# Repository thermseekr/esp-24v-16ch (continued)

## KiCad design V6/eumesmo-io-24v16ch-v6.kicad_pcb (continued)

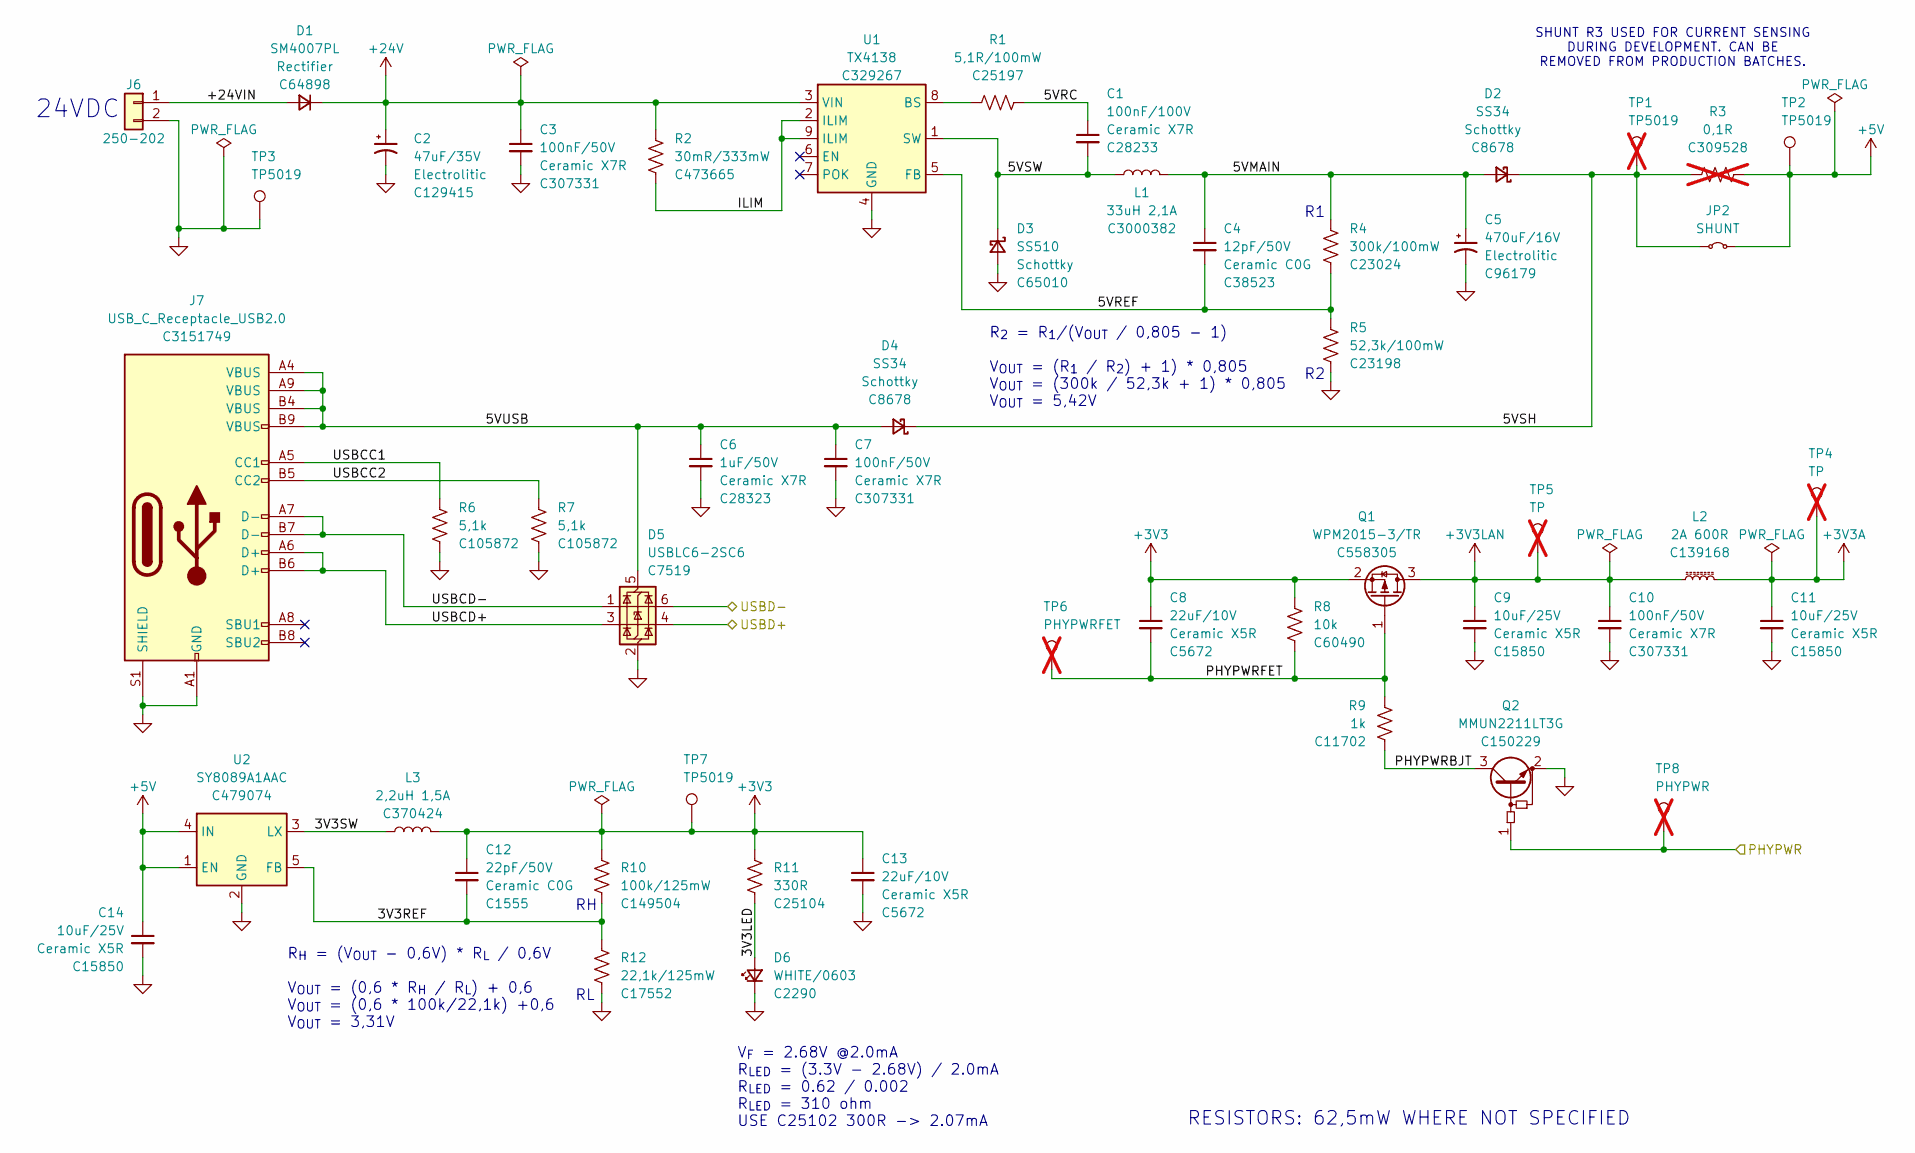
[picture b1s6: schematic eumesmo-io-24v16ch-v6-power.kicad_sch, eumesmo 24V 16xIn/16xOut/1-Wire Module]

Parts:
C1: 100nF/100V; C_0805_2012Metric; Mfr PN CL21B104KCFNNNE; LCSC Part # C28233
C2: 47uF/35V; CP_Elec_6.3x5.4; Mfr PN CK1V470M-CRE54; LCSC Part # C129415
C3, C7, C10: 100nF/50V; C_0402_1005Metric; Mfr PN CL05B104KB54PNC; LCSC Part # C307331
C4: 12pF/50V; C_0603_1608Metric; Mfr PN CL10C120JB8NNNC; LCSC Part # C38523
C5: 470uF/16V; CP_Elec_8x10.5; Mfr PN CS1C471M-CRF10; LCSC Part # C96179
C6: 1uF/50V; C_0805_2012Metric; Mfr PN CL21B105KBFNNNE; LCSC Part # C28323
C8, C13: 22uF/10V; C_1206_3216Metric; Mfr PN CL31A226KPHNNNE; LCSC Part # C5672
C9, C11, C14: 10uF/25V; C_0805_2012Metric; Mfr PN CL21A106KAYNNNE; LCSC Part # C15850
C12: 22pF/50V; C_0402_1005Metric; Mfr PN 0402CG220J500NT; LCSC Part # C1555
D1: SM4007PL; D_SOD-123; Mfr PN SM4007PL; LCSC Part # C64898
D2, D4: SS34; D_SMA; Mfr PN SS34; LCSC Part # C8678
D3: SS510; D_SMA; Mfr PN SS510; LCSC Part # C65010
D5: USBLC6-2SC6; SOT-23-6; Mfr PN USBLC6-2SC6; LCSC Part # C7519
D6: WHITE/0603; LED_0603_1608Metric; Mfr PN KT-0603W; LCSC Part # C2290
J6: 250-202; TerminalBlock_Wago_250-202_1x02_P3.5mm_45Degree; Mfr PN 250-202; LCSC Part # C2765061
J7: USB_C_Receptacle_USB2.0; USB_C_Receptacle_ShouHan_TYPE-C-16PLT-H10.0; Mfr PN TYPE-C 16PLT-H10.0; LCSC Part # C3151749
JP2: SHUNT; SolderJumper-2_P1.3mm_Bridged_RoundedPad1.0x1.5mm
L1: 33uH 2,1A; L_12x12mm_H6mm; Mfr PN SMDRI125-330MT; LCSC Part # C3000382
L2: 2A 600R; L_0805_2012Metric; Mfr PN CBM201209U601T; LCSC Part # C139168
L3: 2,2uH 1,5A; L_3x3mm_H1.5mm; Mfr PN SPH3015H2R2MT; LCSC Part # C370424
Q1: WPM2015-3/TR; SOT-23; Mfr PN WPM2015-3/TR; LCSC Part # C558305
Q2: MMUN2211LT3G; SOT-23; Mfr PN MMUN2211LT3G; LCSC Part # C150229
R1: 5,1R/100mW; R_0603_1608Metric; Mfr PN 0603WAF510KT5E; LCSC Part # C25197
R2: 30mR/333mW; R_1206_3216Metric; Mfr PN 1206W3F300MT5E; LCSC Part # C473665
R3: 0,1R; C_1206_3216Metric; Mfr PN PE1206FRF470R1L; LCSC Part # C309528; not fitted
R4: 300k/100mW; R_0603_1608Metric; Mfr PN 0603WAF3003T5E; LCSC Part # C23024
R5: 52,3k/100mW; R_0603_1608Metric; Mfr PN 0603WAF5232T5E; LCSC Part # C23198
R6, R7: 5,1k; R_0402_1005Metric; Mfr PN RC0402FR-075K1L; LCSC Part # C105872
R8: 10k; R_0402_1005Metric; Mfr PN RC0402FR-0710KL; LCSC Part # C60490
R9: 1k; R_0402_1005Metric; Mfr PN 0402WGF1001TCE; LCSC Part # C11702
R10: 100k/125mW; R_0805_2012Metric; Mfr PN 0805W8F1003T5E; LCSC Part # C149504
R11: 330R; R_0402_1005Metric; Mfr PN 0402WGF3300TCE; LCSC Part # C25104
R12: 22,1k/125mW; R_0805_2012Metric; Mfr PN 0805W8F2212T5E; LCSC Part # C17552
TP1: TP5019; TestPoint_Keystone_5019_Miniature; Mfr PN 5019; LCSC Part # C238131; not fitted
TP2, TP3, TP7: TP5019; TestPoint_Keystone_5019_Miniature; Mfr PN 5019; LCSC Part # C238131
TP4, TP5: TP; TestPoint_Pad_D1.5mm; not fitted
TP6: PHYPWRFET; TestPoint_Pad_D1.5mm; not fitted
TP8: PHYPWR; TestPoint_Pad_D1.5mm; not fitted
U1: TX4138; SOIC-8-1EP_3.9x4.9mm_P1.27mm_EP2.41x3.81mm_ThermalVias; Mfr PN TX4138; LCSC Part # C329267
U2: SY8089A1AAC; SOT-23-5_Shorter_Pins; Mfr PN SY8089A1AAC; LCSC Part # C479074

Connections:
+3V3: C8.1, C12.1, C13.1, L3.2, Q1.2 (S), R8.1, R10.1, R11.1, TP7.1 (1_1); also elsewhere on the board
+3V3A: C11.1, L2.2, TP4.1; also elsewhere on the board
+3V3LAN: C9.1, C10.1, L2.1, Q1.3 (D), TP5.1; also elsewhere on the board
+5V: C14.1, JP2.2 (B), R3.1, TP2.1 (1_1), U2.1 (EN), U2.4 (IN); also elsewhere on the board
+24V: C2.1, C3.1, D1.1 (K), R2.1, U1.3 (VIN); also elsewhere on the board
/MCU/PHYPWR: Q2.1 (B), TP8.1; also elsewhere on the board
/MCU/USBD+: D5.4 (I/O2); also elsewhere on the board
/MCU/USBD-: D5.6 (I/O1); also elsewhere on the board
/Power/3V3LED: D6.2 (A), R11.2
/Power/3V3REF: C12.2, R10.2, R12.1, U2.5 (FB)
/Power/3V3SW: L3.1, U2.3 (LX)
/Power/5VMAIN: C4.1, C5.1, D2.2 (A), L1.2, R4.1
/Power/5VRC: C1.1, R1.1
/Power/5VREF: C4.2, R4.2, R5.1, U1.5 (FB)
/Power/5VSH: D2.1 (K), D4.1 (K), JP2.1 (A), R3.2, TP1.1
/Power/5VSW: C1.2, D3.1 (K), L1.1, U1.1 (SW)
/Power/5VUSB: C6.1, C7.1, D4.2 (A), D5.5 (VBUS), J7.A4 (VBUS), J7.A9 (VBUS), J7.B4 (VBUS), J7.B9 (VBUS)
/Power/+24VIN: D1.2 (A), J6.1
/Power/ILIM: R2.2, U1.2 (ILIM), U1.9 (ILIM)
/Power/PHYPWRBJT: Q2.3 (C), R9.1
/Power/PHYPWRFET: C8.2, Q1.1 (G), R8.2, R9.2, TP6.1
/Power/USBCC1: J7.A5 (CC1), R6.1
/Power/USBCC2: J7.B5 (CC2), R7.1
/Power/USBCD+: D5.3 (I/O2), J7.A6 (D+), J7.B6 (D+)
/Power/USBCD-: D5.1 (I/O1), J7.A7 (D-), J7.B7 (D-)
GND: C2.2, C3.2, C5.2, C6.2, C7.2, C9.2, C10.2, C11.2, C13.2, C14.2, D3.2 (A), D5.2 (GND), D6.1 (K), J6.2, J7.A1 (GND), J7.A12 (GND), J7.B1 (GND), J7.B12 (GND), J7.S1 (SHIELD), Q2.2 (E), R5.2, R6.2, R7.2, R12.2, TP3.1 (1_1), U1.4 (GND), U2.2 (GND); also elsewhere on the board
unnamed: R1.2, U1.8 (BS)

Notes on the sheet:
RESISTORS: 62,5mW WHERE NOT SPECIFIED
V_{F} = 2.68V @2.0mA R_{LED} = (3.3V - 2.68V) / 2.0mA R_{LED} = 0.62 / 0.002 R_{LED} = 310 ohm USE C25102 300R -> 2.07mA
R_{H} = (V_{OUT} - 0,6V) * R_{L} / 0,6V V_{OUT} = (0,6 * R_{H} / R_{L}) + 0,6 V_{OUT} = (0,6 * 100k/22,1k) +0,6 V_{OUT} = 3,31V
R_{2} = R_{1}/(V_{OUT} / 0,805 - 1) V_{OUT} = (R_{1} / R_{2}) + 1) * 0,805 V_{OUT} = (300k / 52,3k + 1) * 0,805 V_{OUT} = 5,42V
SHUNT R3 USED FOR CURRENT SENSING DURING DEVELOPMENT. CAN BE REMOVED FROM PRODUCTION BATCHES.
24VDC

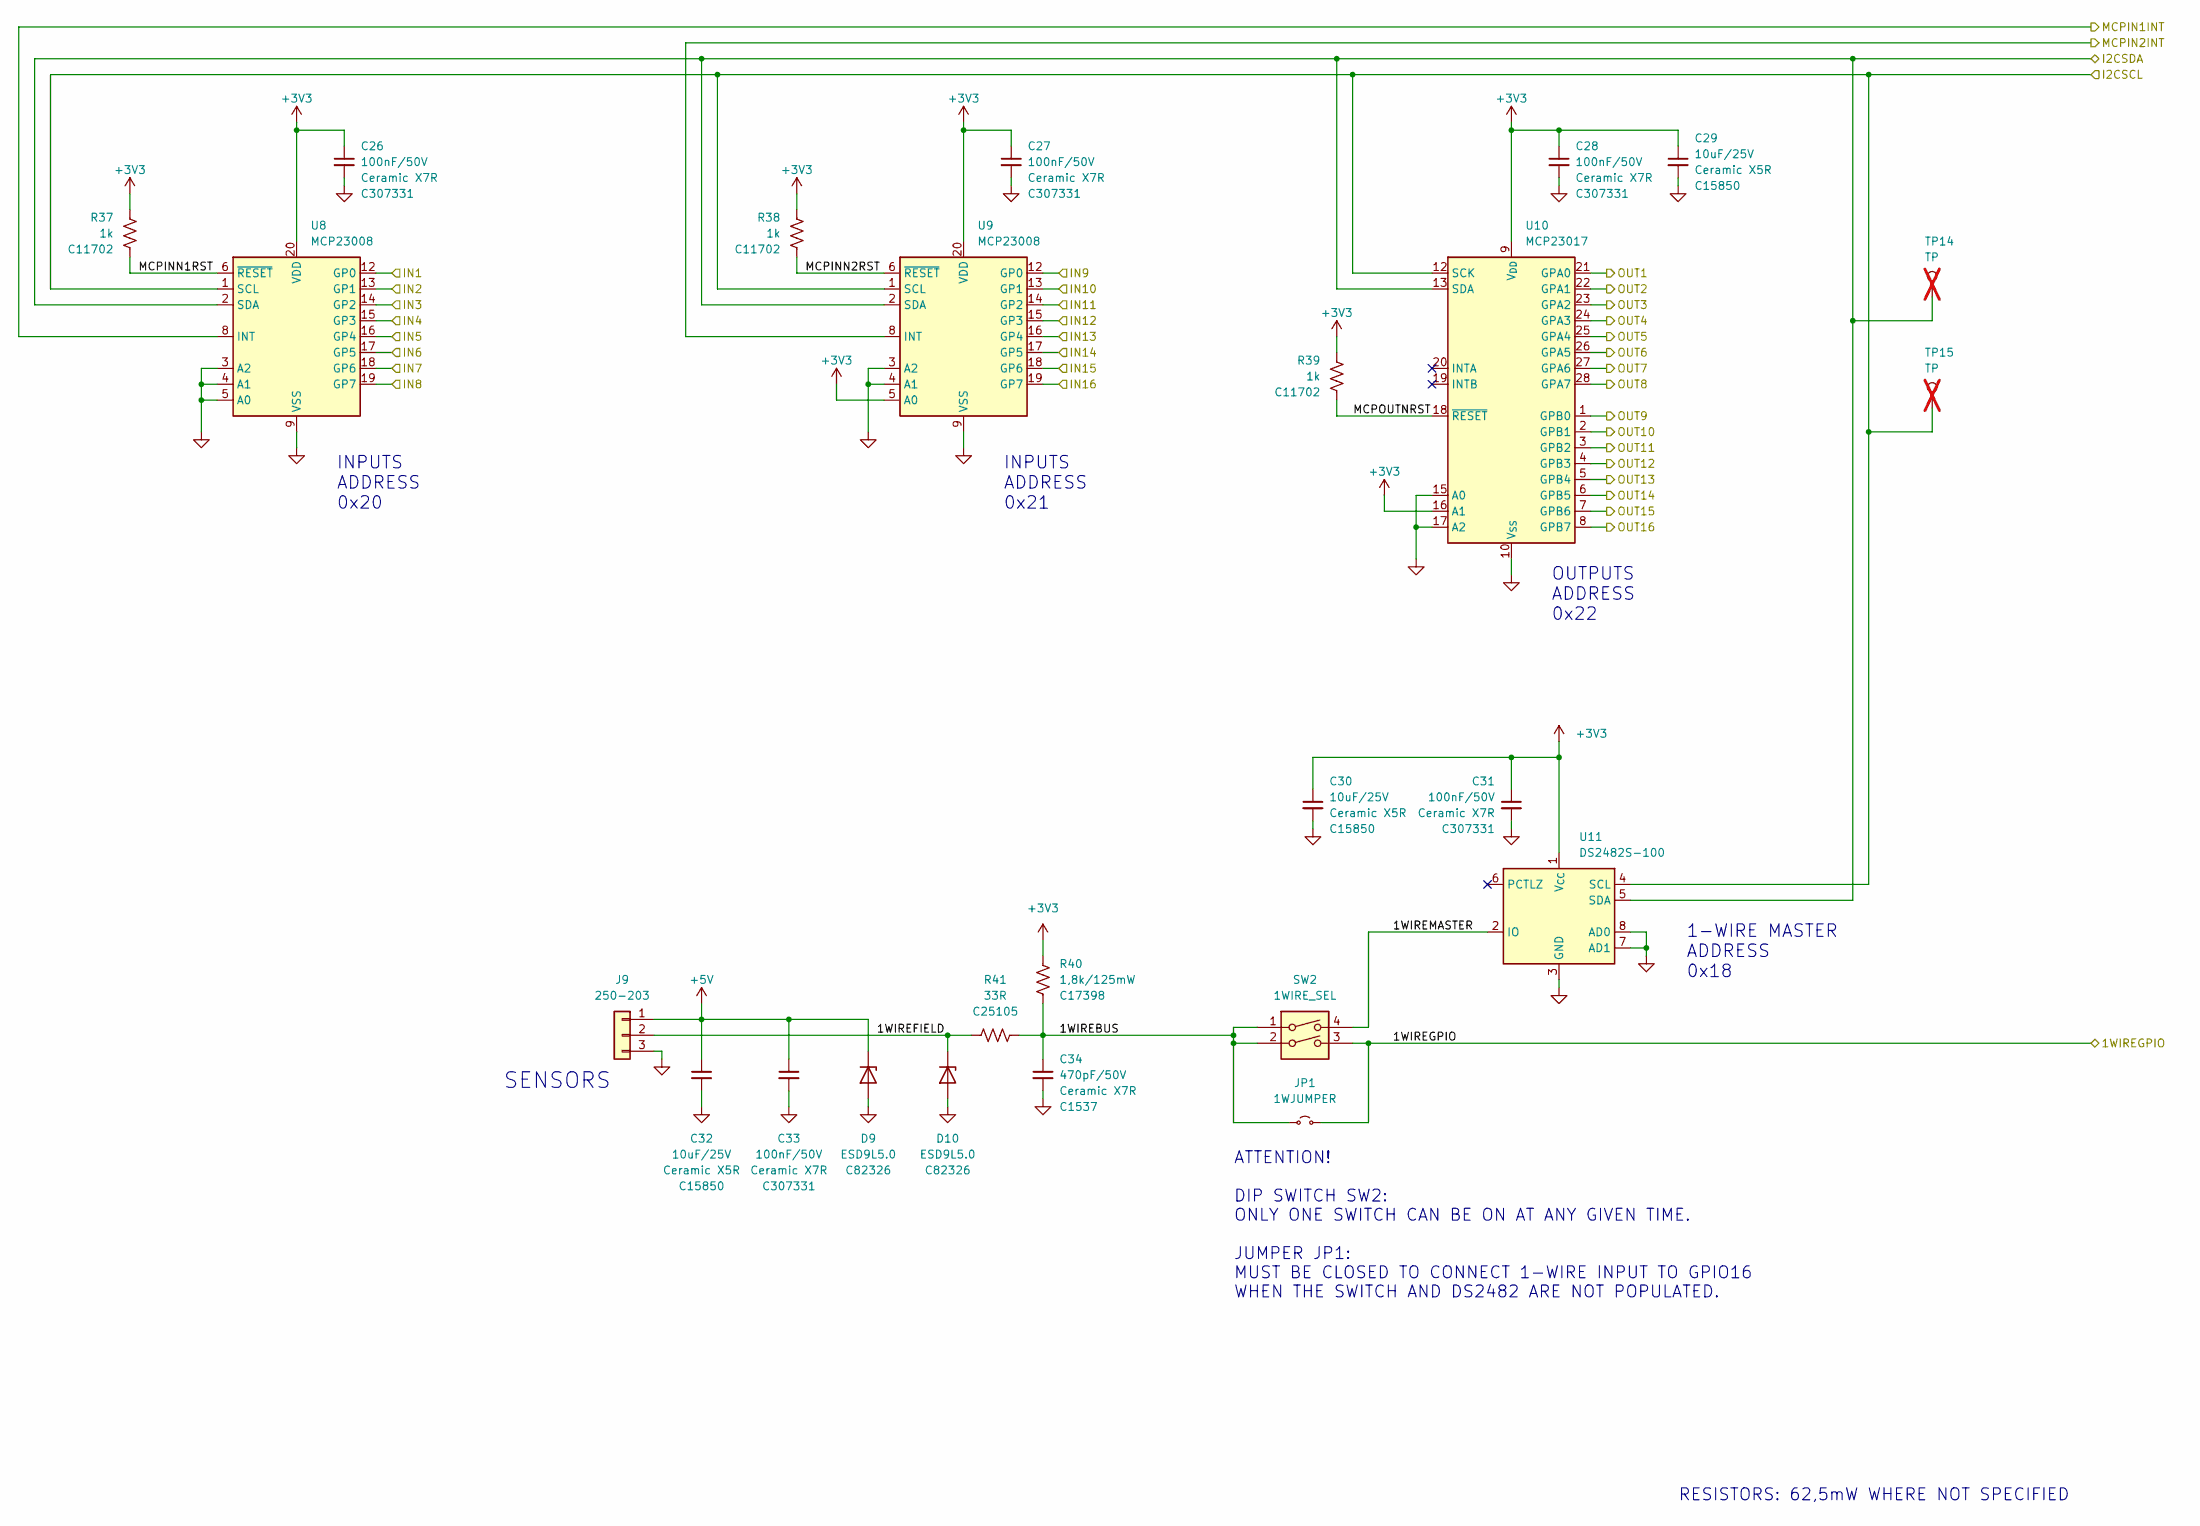
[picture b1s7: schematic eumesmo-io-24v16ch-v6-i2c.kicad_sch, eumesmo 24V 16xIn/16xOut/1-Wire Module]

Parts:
C26, C27, C28, C31, C33: 100nF/50V; C_0402_1005Metric; Mfr PN CL05B104KB54PNC; LCSC Part # C307331
C29, C30, C32: 10uF/25V; C_0805_2012Metric; Mfr PN CL21A106KAYNNNE; LCSC Part # C15850
C34: 470pF/50V; C_0402_1005Metric; Mfr PN 0402B471K500NT; LCSC Part # C1537
D9, D10: ESD9L5.0; D_SOD-923; Mfr PN ESD9L5.0ST5G; LCSC Part # C82326
J9: 250-203; TerminalBlock_Wago_250-203_1x03_P3.5mm_45Degree; Mfr PN 250-203; LCSC Part # C2765062
JP1: 1WJUMPER; SolderJumper-2_P1.3mm_Open_RoundedPad1.0x1.5mm
R37, R38, R39: 1k; R_0402_1005Metric; Mfr PN 0402WGF1001TCE; LCSC Part # C11702
R40: 1,8k/125mW; R_0805_2012Metric; Mfr PN 0805W8F1801T5E; LCSC Part # C17398
R41: 33R; R_0402_1005Metric; Mfr PN 0402WGF330JTCE; LCSC Part # C25105
SW2: 1WIRE_SEL; SW_DIP_SPSTx02_Slide_Copal_CHS-02B_W7.62mm_P1.27mm; Mfr PN DSHP02TS-S; LCSC Part # C319052
TP14, TP15: TP; TestPoint_Pad_D1.5mm; not fitted
U8, U9: MCP23008; SSOP-20_5.3x7.2mm_P0.65mm; Mfr PN MCP23008-E/SS; LCSC Part # C148011
U10: MCP23017; SSOP-28_5.3x10.2mm_P0.65mm; Mfr PN MCP23017-E/SS; LCSC Part # C506653
U11: DS2482S-100; SO-8_3.9x4.9mm_P1.27mm; Mfr PN DS2482S-100; LCSC Part # C143306

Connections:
+3V3: C26.1, C27.1, C28.1, C29.1, C30.1, C31.1, R37.1, R38.1, R39.1, R40.1, U8.20 (VDD), U9.5 (A0), U9.20 (VDD), U10.9 (V_{DD}), U10.16 (A1), U11.1 (V_{CC}); also elsewhere on the board
+5V: C32.1, C33.1, D9.1 (K), J9.1; also elsewhere on the board
/I2C Devices/1WIREBUS: C34.1, JP1.1 (A), R40.2, R41.2, SW2.1, SW2.2
/I2C Devices/1WIREFIELD: D10.1 (K), J9.2, R41.1
/I2C Devices/1WIREGPIO: JP1.2 (B), SW2.3; also elsewhere on the board
/I2C Devices/1WIREMASTER: SW2.4, U11.2 (IO)
/I2C Devices/I2CSCL: TP15.1, U8.1 (SCL), U9.1 (SCL), U10.12 (SCK), U11.4 (SCL); also elsewhere on the board
/I2C Devices/I2CSDA: TP14.1, U8.2 (SDA), U9.2 (SDA), U10.13 (SDA), U11.5 (SDA); also elsewhere on the board
/I2C Devices/MCPIN1INT: U8.8 (INT); also elsewhere on the board
/I2C Devices/MCPIN2INT: U9.8 (INT); also elsewhere on the board
/I2C Devices/MCPINN1RST: R37.2, U8.6 (~RESET)
/I2C Devices/MCPINN2RST: R38.2, U9.6 (~RESET)
/I2C Devices/MCPOUTNRST: R39.2, U10.18 (~RESET)
/INPUT1: U8.12 (GP0); also elsewhere on the board
/INPUT2: U8.13 (GP1); also elsewhere on the board
/INPUT3: U8.14 (GP2); also elsewhere on the board
/INPUT4: U8.15 (GP3); also elsewhere on the board
/INPUT5: U8.16 (GP4); also elsewhere on the board
/INPUT6: U8.17 (GP5); also elsewhere on the board
/INPUT7: U8.18 (GP6); also elsewhere on the board
/INPUT8: U8.19 (GP7); also elsewhere on the board
/INPUT9: U9.12 (GP0); also elsewhere on the board
/INPUT10: U9.13 (GP1); also elsewhere on the board
/INPUT11: U9.14 (GP2); also elsewhere on the board
/INPUT12: U9.15 (GP3); also elsewhere on the board
/INPUT13: U9.16 (GP4); also elsewhere on the board
/INPUT14: U9.17 (GP5); also elsewhere on the board
/INPUT15: U9.18 (GP6); also elsewhere on the board
/INPUT16: U9.19 (GP7); also elsewhere on the board
/OUTPUT1: U10.21 (GPA0); also elsewhere on the board
/OUTPUT2: U10.22 (GPA1); also elsewhere on the board
/OUTPUT3: U10.23 (GPA2); also elsewhere on the board
/OUTPUT4: U10.24 (GPA3); also elsewhere on the board
/OUTPUT5: U10.25 (GPA4); also elsewhere on the board
/OUTPUT6: U10.26 (GPA5); also elsewhere on the board
/OUTPUT7: U10.27 (GPA6); also elsewhere on the board
/OUTPUT8: U10.28 (GPA7); also elsewhere on the board
/OUTPUT9: U10.1 (GPB0); also elsewhere on the board
/OUTPUT10: U10.2 (GPB1); also elsewhere on the board
/OUTPUT11: U10.3 (GPB2); also elsewhere on the board
/OUTPUT12: U10.4 (GPB3); also elsewhere on the board
/OUTPUT13: U10.5 (GPB4); also elsewhere on the board
/OUTPUT14: U10.6 (GPB5); also elsewhere on the board
/OUTPUT15: U10.7 (GPB6); also elsewhere on the board
/OUTPUT16: U10.8 (GPB7); also elsewhere on the board
GND: C26.2, C27.2, C28.2, C29.2, C30.2, C31.2, C32.2, C33.2, C34.2, D9.2 (A), D10.2 (A), J9.3, U8.3 (A2), U8.4 (A1), U8.5 (A0), U8.9 (VSS), U9.3 (A2), U9.4 (A1), U9.9 (VSS), U10.10 (V_{SS}), U10.15 (A0), U10.17 (A2), U11.3 (GND), U11.7 (AD1), U11.8 (AD0); also elsewhere on the board

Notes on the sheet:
OUTPUTS ADDRESS 0x22
INPUTS ADDRESS 0x20
RESISTORS: 62,5mW WHERE NOT SPECIFIED
1-WIRE MASTER ADDRESS 0x18
INPUTS ADDRESS 0x21
ATTENTION! DIP SWITCH SW2: ONLY ONE SWITCH CAN BE ON AT ANY GIVEN TIME. JUMPER JP1: MUST BE CLOSED TO CONNECT 1-WIRE INPUT TO GPIO16 WHEN THE SWITCH AND DS2482 ARE NOT POPULATED.
SENSORS

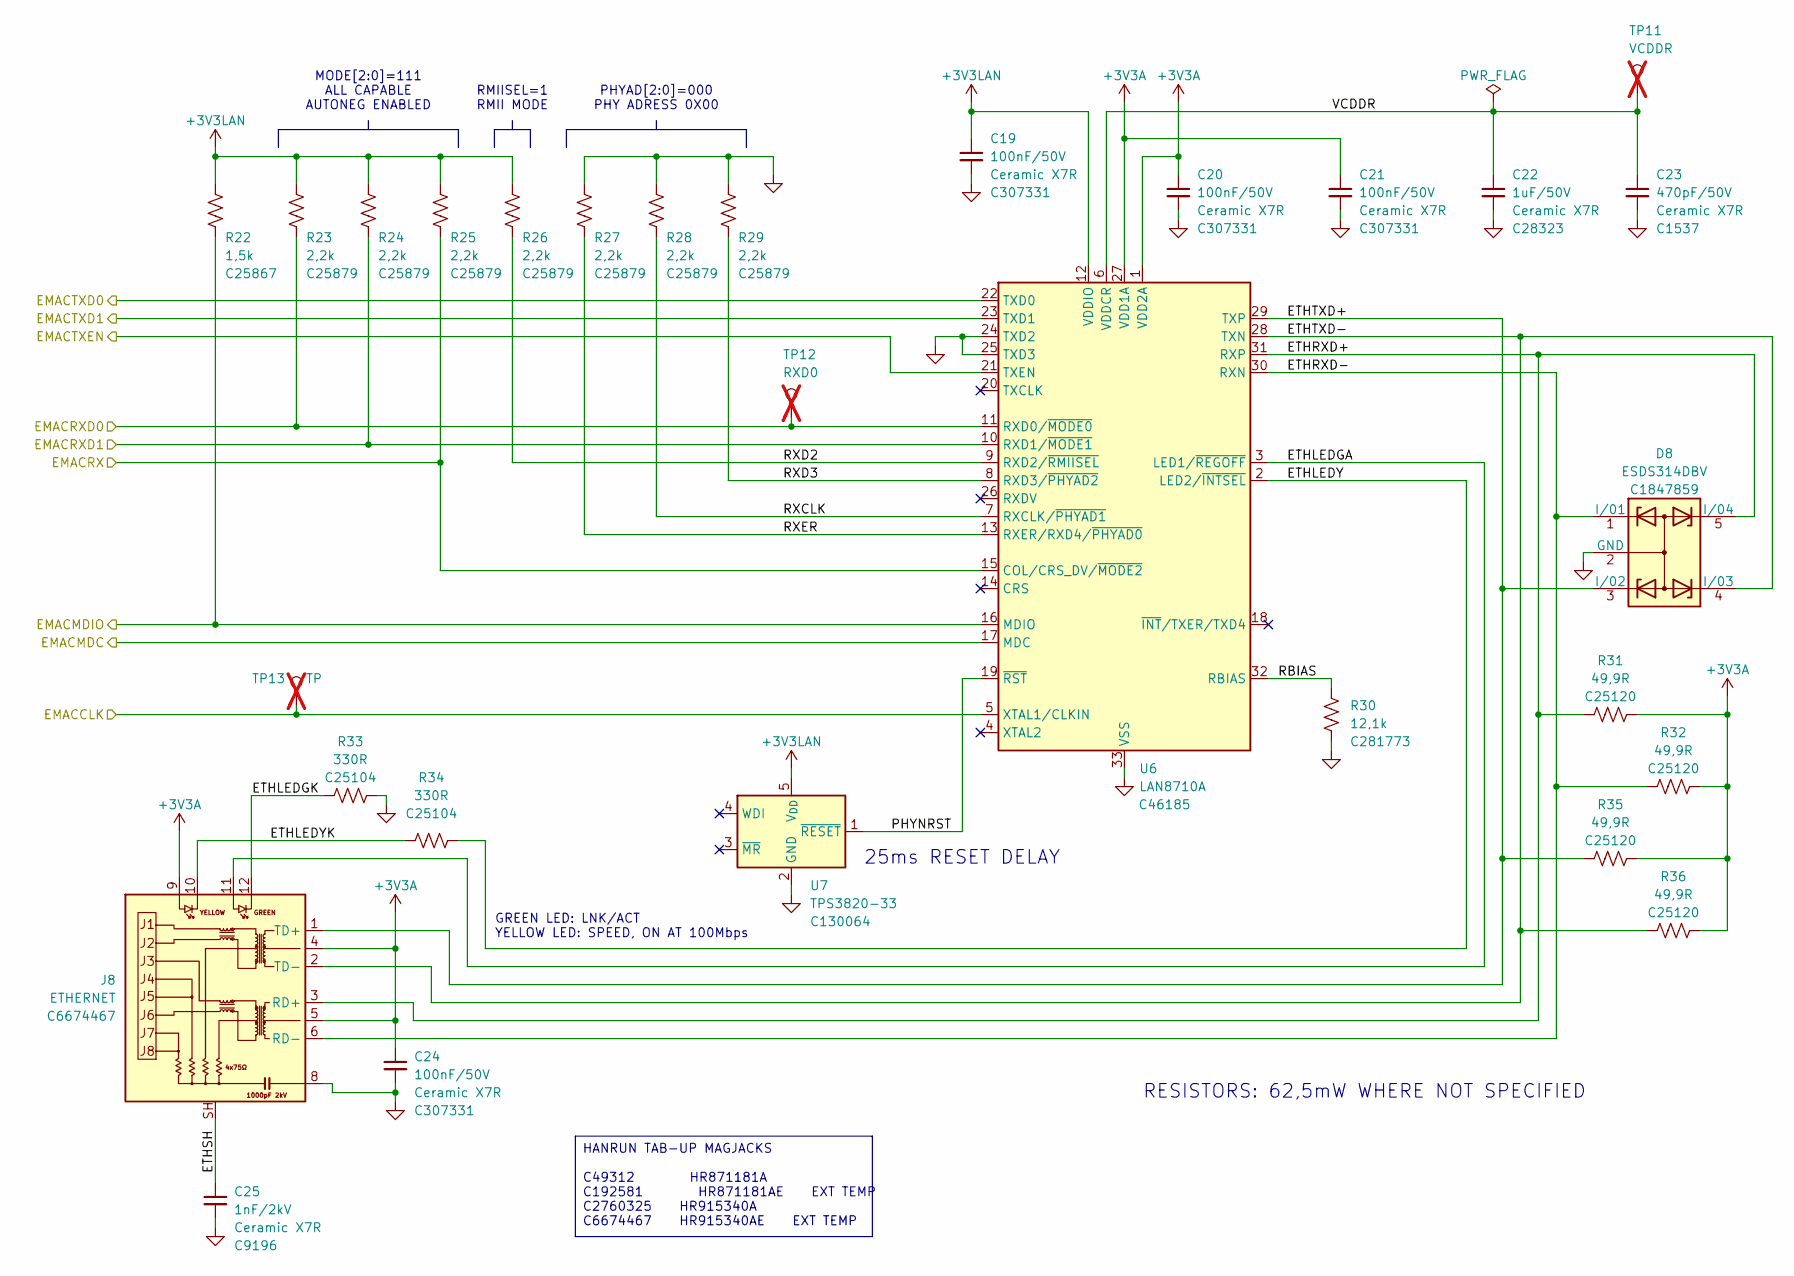
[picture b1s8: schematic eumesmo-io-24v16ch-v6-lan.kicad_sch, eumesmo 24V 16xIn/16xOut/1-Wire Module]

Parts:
C19, C20, C21, C24: 100nF/50V; C_0402_1005Metric; Mfr PN CL05B104KB54PNC; LCSC Part # C307331
C22: 1uF/50V; C_0805_2012Metric; Mfr PN CL21B105KBFNNNE; LCSC Part # C28323
C23: 470pF/50V; C_0402_1005Metric; Mfr PN 0402B471K500NT; LCSC Part # C1537
C25: 1nF/2kV; C_1206_3216Metric; Mfr PN 1206B102K202NT; LCSC Part # C9196
D8: ESDS314DBV; SOT-23-5; Mfr PN ESDS314DBVR; LCSC Part # C1847859
J8: ETHERNET; RJ45_HanRun_HR915340A; Mfr PN HR915340AE; LCSC Part # C6674467
R22: 1,5k; R_0402_1005Metric; Mfr PN 0402WGF1501TCE; LCSC Part # C25867
R23, R24, R25, R26, R27, R28, R29: 2,2k; R_0402_1005Metric; Mfr PN 0402WGF2201TCE; LCSC Part # C25879
R30: 12,1k; R_0402_1005Metric; Mfr PN RT0402BRD0712K1L; LCSC Part # C281773
R31, R32, R35, R36: 49,9R; R_0402_1005Metric; Mfr PN 0402WGF499JTCE; LCSC Part # C25120
R33, R34: 330R; R_0402_1005Metric; Mfr PN 0402WGF3300TCE; LCSC Part # C25104
TP11: VCDDR; TestPoint_Pad_D1.5mm; not fitted
TP12: RXD0; TestPoint_Pad_D1.5mm; not fitted
TP13: TP; TestPoint_Pad_D1.5mm; not fitted
U6: LAN8710A; QFN-32-1EP_5x5mm_P0.5mm_EP3.3x3.3mm_ThermalVias; Mfr PN LAN8710A-EZC-TR; LCSC Part # C46185
U7: TPS3820-33; SOT-23-5; Mfr PN TPS3820-33DBVR; LCSC Part # C130064

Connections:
+3V3A: C20.1, C21.1, C24.1, J8.4, J8.5, J8.9, R31.2, R32.2, R35.2, R36.2, U6.1 (VDD2A), U6.27 (VDD1A); also elsewhere on the board
+3V3LAN: C19.1, R22.1, R23.1, R24.1, R25.1, R26.1, U6.12 (VDDIO), U7.5 (V_{DD}); also elsewhere on the board
/LAN/EMACCLK: TP13.1, U6.5 (XTAL1/CLKIN); also elsewhere on the board
/LAN/EMACMDC: U6.17 (MDC); also elsewhere on the board
/LAN/EMACMDIO: R22.2, U6.16 (MDIO); also elsewhere on the board
/LAN/EMACRX: R25.2, U6.15 (COL/CRS_DV/~MODE2); also elsewhere on the board
/LAN/EMACRXD0: R23.2, U6.11 (RXD0/~MODE0); also elsewhere on the board
/LAN/EMACRXD1: R24.2, U6.10 (RXD1/~MODE1); also elsewhere on the board
/LAN/EMACTXD0: U6.22 (TXD0); also elsewhere on the board
/LAN/EMACTXD1: U6.23 (TXD1); also elsewhere on the board
/LAN/EMACTXEN: U6.21 (TXEN); also elsewhere on the board
/LAN/ETHLEDGA: J8.11, U6.3 (LED1/~REGOFF)
/LAN/ETHLEDGK: J8.12, R33.1
/LAN/ETHLEDY: R34.2, U6.2 (LED2/~INTSEL)
/LAN/ETHLEDYK: J8.10, R34.1
/LAN/ETHRXD+: D8.5 (I/04), J8.3 (RD+), R31.1, U6.31 (RXP)
/LAN/ETHRXD-: D8.1 (I/01), J8.6 (RD-), R32.1, U6.30 (RXN)
/LAN/ETHSH: C25.1, J8.SH
/LAN/ETHTXD+: D8.3 (I/02), J8.1 (TD+), R35.1, U6.29 (TXP)
/LAN/ETHTXD-: D8.4 (I/03), J8.2 (TD-), R36.1, U6.28 (TXN)
/LAN/PHYNRST: U6.19 (~RST), U7.1 (~RESET)
/LAN/RBIAS: R30.1, U6.32 (RBIAS)
/LAN/RXCLK: R28.2, U6.7 (RXCLK/~PHYAD1)
/LAN/RXD2: R26.2, U6.9 (RXD2/~RMIISEL)
/LAN/RXD3: R29.2, U6.8 (RXD3/~PHYAD2)
/LAN/RXER: R27.2, U6.13 (RXER/RXD4/~PHYAD0)
/LAN/VCDDR: C22.1, C23.1, U6.6 (VDDCR)
GND: C19.2, C20.2, C21.2, C22.2, C23.2, C24.2, C25.2, D8.2 (GND), J8.8, R27.1, R28.1, R29.1, R30.2, R33.2, U6.24 (TXD2), U6.25 (TXD3), U6.33 (VSS), U7.2 (GND); also elsewhere on the board

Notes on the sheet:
25ms RESET DELAY
GREEN LED: LNK/ACT YELLOW LED: SPEED, ON AT 100Mbps
MODE[2:0]=111 ALL CAPABLE AUTONEG ENABLED
PHYAD[2:0]=000 PHY ADRESS 0X00
RMIISEL=1 RMII MODE
RESISTORS: 62,5mW WHERE NOT SPECIFIED
HANRUN TAB-UP MAGJACKS C49312 HR871181A C192581 HR871181AE EXT TEMP C2760325 HR915340A C6674467 HR915340AE EXT TEMP

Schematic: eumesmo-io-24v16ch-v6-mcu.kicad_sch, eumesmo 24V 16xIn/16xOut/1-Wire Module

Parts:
C15, C17: 10uF/25V; C_0805_2012Metric; Mfr PN CL21A106KAYNNNE; LCSC Part # C15850
C16, C18: 100nF/50V; C_0402_1005Metric; Mfr PN CL05B104KB54PNC; LCSC Part # C307331
D7: WHITE/0603; LED_0603_1608Metric; Mfr PN KT-0603W; LCSC Part # C2290
Q3: UMH3N; SOT-363_SC-70-6; Mfr PN UMH3N; LCSC Part # C62892
R13: 330R; R_0402_1005Metric; Mfr PN 0402WGF3300TCE; LCSC Part # C25104
R14, R15, R18: 10k; R_0402_1005Metric; Mfr PN RC0402FR-0710KL; LCSC Part # C60490
R16, R17, R20, R21: 2,2k; R_0402_1005Metric; Mfr PN 0402WGF2201TCE; LCSC Part # C25879
R19: 33R; R_0402_1005Metric; Mfr PN 0402WGF330JTCE; LCSC Part # C25105
SW1: RESET; SW_SPST_Xunpu_TS1088AR02016; Mfr PN TS-1088-AR02016; LCSC Part # C720477
TP9, TP10: TP; TestPoint_Pad_D1.5mm; not fitted
U3: TPS3820-33; SOT-23-5; Mfr PN TPS3820-33DBVR; LCSC Part # C130064
U4: CH340K; SSOP-10-1EP_3.9x4.9mm_P1mm_EP2.1x3.3mm; Mfr PN CH340K; LCSC Part # C968586
U5: ESP32-WROOM-32UE-N16; ESP32-WROOM-32U; Mfr PN ESP32-WROOM-32UE-N16; LCSC Part # C701346

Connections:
+3V3: C15.1, C16.1, C17.1, C18.1, R14.1, R15.1, R16.1, R17.1, R20.1, R21.1, U3.5 (V_{DD}), U4.7 (VCC), U4.10 (V3), U5.2 (VDD); also elsewhere on the board
/I2C Devices/1WIREGPIO: U5.27 (IO16); also elsewhere on the board
/I2C Devices/I2CSCL: R20.2, U5.8 (IO32); also elsewhere on the board
/I2C Devices/I2CSDA: R21.2, U5.9 (IO33); also elsewhere on the board
/I2C Devices/MCPIN1INT: R16.2, U5.16 (IO13); also elsewhere on the board
/I2C Devices/MCPIN2INT: R17.2, U5.13 (IO14); also elsewhere on the board
/LAN/EMACCLK: R19.2, U5.5 (SENSOR_VN); also elsewhere on the board
/LAN/EMACMDC: U5.37 (IO23); also elsewhere on the board
/LAN/EMACMDIO: U5.30 (IO18); also elsewhere on the board
/LAN/EMACRX: U5.12 (IO27); also elsewhere on the board
/LAN/EMACRXD0: U5.10 (IO25); also elsewhere on the board
/LAN/EMACRXD1: U5.11 (IO26); also elsewhere on the board
/LAN/EMACTXD0: U5.31 (IO19); also elsewhere on the board
/LAN/EMACTXD1: U5.36 (IO22); also elsewhere on the board
/LAN/EMACTXEN: U5.33 (IO21); also elsewhere on the board
/MCU/CPULED: D7.2 (A), R13.2
/MCU/CPUOK: R13.1, U5.24 (IO2)
/MCU/ESPCLK: R19.1, U5.28 (IO17)
/MCU/ESPEN: U3.1 (~RESET), U5.3 (EN)
/MCU/ESPPROG: Q3.3 (C2), R15.2, U5.25 (IO0)
/MCU/MRESET: Q3.6 (C1), R14.2, SW1.2, U3.3 (~MR)
/MCU/PHYPWR: R18.1, U5.14 (IO12); also elsewhere on the board
/MCU/UARTNDTR: Q3.2 (B1), Q3.4 (E2), U4.4 (~DTR)
/MCU/UARTNRTS: Q3.1 (E1), Q3.5 (B2), U4.6 (~RTS)
/MCU/UARTRXD: U4.9 (RXD), U5.35 (TXD0/IO1)
/MCU/UARTTXD: U4.8 (TXD), U5.34 (RXD0/IO3)
/MCU/USBD+: TP9.1, U4.1 (UD+); also elsewhere on the board
/MCU/USBD-: TP10.1, U4.2 (UD-); also elsewhere on the board
GND: C15.2, C16.2, C17.2, C18.2, D7.1 (K), R18.2, SW1.1, U3.2 (GND), U4.3 (GND), U4.11 (GND), U5.1 (GND), U5.15 (GND), U5.38 (GND), U5.39 (GND); also elsewhere on the board

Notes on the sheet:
TASMOTA CONFIGS The configs below must be applied via terminal/console and adjusted according to the desired hostname, device name, network addresses and behavior of switches. Configure switches: > backlog switchmode1 5; switchmode2 5; switchmode3 5; switchmode4 5; switchmode5 5; switchmode6 5; swi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
25ms RESET DELAY
TEMPLATE FOR GPIO ASSIGNMENT {"NAME":"eumesmo-io-24v16ch-v6","GPIO":[0,3200,0,3232,0,0,0,0,5536,10240,10241,0,1312, 0,5600,0,0,0,0,5568,0,0,0,0,0,0,0,0,608,640,0,0,0,0,0,0],"FLAG":0,"BASE":1} See https://tasmota.github.io/docs/Templates/
TEMPLATE FOR MCP23017 I/O ASSIGNMENT {"NAME":"MCP23017 expanders","BASE":0,"GPIO":[192,193,194,195,196,197,198,199,200,201, 202,203,204,205,206,207,224,225,226,227,228,229,230,231,232,233,234,235,236,237,238, 239],"IOCON":0x5C} Save as mcp23x.dat and load into tasmota's filesystem. See https://tasm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
RESISTORS: 62,5mW WHERE NOT SPECIFIED
ESP32 GPIO ASSIGNMENT PIN PORT FUNCTION COMPONENT 25 GPIO0 AUTO FLASH MODE 0 35 GPIO1 SERIAL TX 3200 24 GPIO2 - 0 34 GPIO3 SERIAL RX 3232 26 GPIO4 - 0 29 GPIO5 - 0 17 GPIO9 - 0 18 GPIO10 - 0 14 GPIO12 ETH POWER 5536 16 GPIO13 MCP23017 INT1 10240 13 GPIO14 MCP23017 INT2 10241 23 GPIO15 - 0 27 GPIO16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

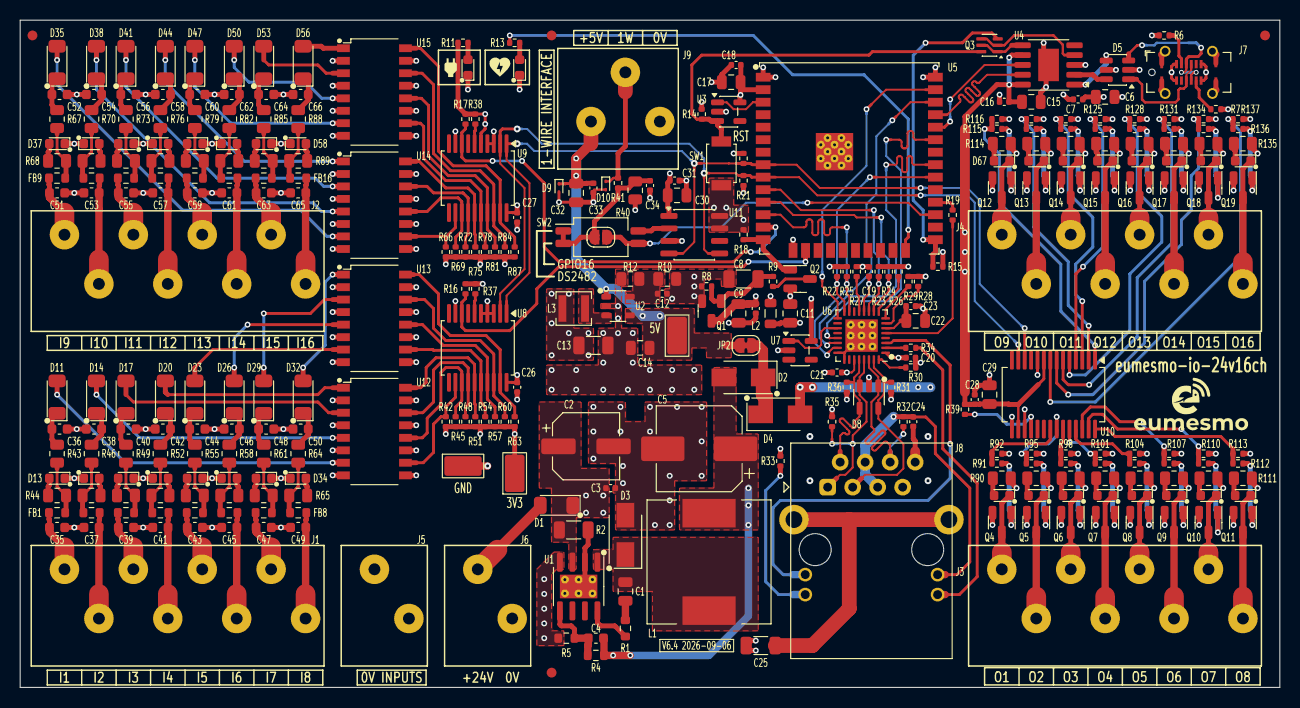
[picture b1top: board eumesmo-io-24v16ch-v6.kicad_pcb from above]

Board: 4 copper layers, 128.0 x 67.8 mm, 333 parts (0 on the bottom side), 234 nets.

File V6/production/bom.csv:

Designator,Footprint,Quantity,Value,LCSC Part #
C1,0805,1,100nF/100V,C28233
"C10, C16, C18, C19, C20, C21, C24, C26, C27, C28, C3, C31, C33, C7",0402,14,100nF/50V,C307331
"C11, C14, C15, C17, C29, C30, C32, C9",0805,8,10uF/25V,C15850
C12,0402,1,22pF/50V,C1555
"C13, C8",1206,2,22uF/10V,C5672
C2,CP_Elec_6.3x5.4,1,47uF/35V,C129415
"C22, C6",0805,2,1uF/50V,C28323
"C23, C34",0402,2,470pF/50V,C1537
C25,1206,1,1nF/2kV,C9196
"C35, C37, C39, C41, C43, C45, C47, C49, C51, C53, C55, C57, C59, C61, C63, C65",0603,16,1nF/50V,C1588
"C36, C38, C40, C42, C44, C46, C48, C50, C52, C54, C56, C58, C60, C62, C64, C66",0603,16,33nF/50V,C21117
C4,0603,1,12pF/50V,C38523
C5,CP_Elec_8x10.5,1,470uF/16V,C96179
D1,D_SOD-123,1,SM4007PL,C64898
"D10, D9",D_SOD-923,2,ESD9L5.0,C82326
"D11, D14, D17, D20, D23, D26, D29, D32, D35, D38, D41, D44, D47, D50, D53, D56",D_SOD-123,16,9V1/500mW,C19077407
"D13, D16, D19, D22, D25, D28, D31, D34, D37, D40, D43, D46, D49, D52, D55, D58, D59, D6, D60, D61, D62, D63, D64, D65, D66, D67, D68, D69, D7, D70, D71, D72, D73, D74",0603,34,WHITE/0603,C2290
"D2, D4",D_SMA,2,SS34,C8678
D3,D_SMA,1,SS510,C65010
D5,SOT-23-6,1,USBLC6-2SC6,C7519
D8,SOT-23-5,1,ESDS314DBV,C1847859
"FB1, FB10, FB11, FB12, FB13, FB14, FB15, FB16, FB2, FB3, FB4, FB5, FB6, FB7, FB8, FB9",0603,16,600R/100MHz,C85833
"J1, J2, J3, J4",TerminalBlock_Wago_250-208_1x08_P3.5mm_45Degree,4,250-208,C2833587
"J5, J6",TerminalBlock_Wago_250-202_1x02_P3.5mm_45Degree,2,250-202,C2765061
J7,USB_C_Receptacle_ShouHan_TYPE-C-16PLT-H10.0,1,USB_C_Receptacle_USB2.0,C3151749
J8,RJ45_HanRun_HR915340A,1,ETHERNET,C6674467
J9,TerminalBlock_Wago_250-203_1x03_P3.5mm_45Degree,1,250-203,C2765062
JP2,SolderJumper-2_P1.3mm_Bridged_RoundedPad1.0x1.5mm,1,SHUNT,
L1,L_12x12mm_H6mm,1,"33uH 2,1A",C3000382
L2,0805,1,2A 600R,C139168
L3,L_3x3mm_H1.5mm,1,"2,2uH 1,5A",C370424
Q1,SOT-23,1,WPM2015-3/TR,C558305
"Q10, Q11, Q12, Q13, Q14, Q15, Q16, Q17, Q18, Q19, Q4, Q5, Q6, Q7, Q8, Q9",SOT-23-Narrow,16,MMBT2222A,C8512
Q2,SOT-23,1,MMUN2211LT3G,C150229
Q3,SOT-363_SC-70-6,1,UMH3N,C62892
R1,0603,1,"5,1R/100mW",C25197
R10,0805,1,100k/125mW,C149504
"R100, R103, R106, R109, R112, R115, R118, R121, R124, R127, R130, R133, R136, R91, R94, R97",0402,16,470R,C25117
"R101, R104, R107, R110, R113, R116, R119, R122, R125, R128, R131, R134, R137, R14, R15, R18, R8, R92, R95, R98",0402,20,10k,C60490
"R102, R105, R108, R111, R114, R117, R120, R123, R126, R129, R132, R135, R44, R47, R50, R53, R56, R59, R62, R65, R68, R71, R74, R77, R80, R83, R86, R89, R90, R93, R96, R99",0805,32,10k/125mW,C17414
"R11, R13, R33, R34",0402,4,330R,C25104
R12,0805,1,"22,1k/125mW",C17552
"R16, R17, R20, R21, R23, R24, R25, R26, R27, R28, R29, R42, R45, R48, R51, R54, R57, R60, R63, R66, R69, R72, R75, R78, R81, R84, R87",0402,27,"2,2k",C25879
"R19, R41",0402,2,33R,C25105
R2,1206,1,30mR/333mW,C473665
R22,0402,1,"1,5k",C25867
R30,0402,1,"12,1k",C281773
"R31, R32, R35, R36",0402,4,"49,9R",C25120
"R37, R38, R39, R9",0402,4,1k,C11702
R4,0603,1,300k/100mW,C23024
"R40, R43, R46, R49, R52, R55, R58, R61, R64, R67, R70, R73, R76, R79, R82, R85, R88",0805,17,"1,8k/125mW",C17398
R5,0603,1,"52,3k/100mW",C23198
"R6, R7",0402,2,"5,1k",C105872
SW1,SW_SPST_Xunpu_TS1088AR02016,1,RESET,C720477
SW2,SW_DIP_SPSTx02_Slide_Copal_CHS-02B_W7.62mm_P1.27mm,1,1WIRE_SEL,C319052
"TP2, TP3, TP7",TestPoint_Keystone_5019_Miniature,3,TP5019,C238131
U1,SOIC-8-1EP_3.9x4.9mm_P1.27mm_EP2.41x3.81mm_ThermalVias,1,TX4138,C329267
U10,SSOP-28_5.3x10.2mm_P0.65mm,1,MCP23017,C506653
U11,SO-8_3.9x4.9mm_P1.27mm,1,DS2482S-100,C143306
"U12, U13, U14, U15",SOP-16_4.4x10.4mm_P1.27mm,4,OR-3H7-4,C2838427
U2,SOT-23-5_Shorter_Pins,1,SY8089A1AAC,C479074
"U3, U7",SOT-23-5,2,TPS3820-33,C130064
U4,SSOP-10-1EP_3.9x4.9mm_P1mm_EP2.1x3.3mm,1,CH340K,C968586
U5,ESP32-WROOM-32U,1,ESP32-WROOM-32UE-N16,C701346
U6,QFN-32-1EP_5x5mm_P0.5mm_EP3.3x3.3mm_ThermalVias,1,LAN8710A,C46185
"U8, U9",SSOP-20_5.3x7.2mm_P0.65mm,2,MCP23008,C148011
